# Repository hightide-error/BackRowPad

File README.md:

# BackRowPad, by The Devil's Workshop (a.k.a hightide-error)

![][backrowPad]

[backrowPad]: imgs/backRowPad.png "Photo of a fully-assembled BackRowPad with RGB underglow."

A 12-key linear macropad, designed to replace the back row of function keys or just be a stick of keys you can map to stuff. Open-source and powered by QMK.

There are no maintainers! I designed this macropad and I am not selling it as a product! I am not providing any support! But the design works and you can make your own if you want, so here it is.

**Read through this before getting the boards and assembling!**

## Features

- Keys (wow)
- A cool pattern on the switch plate and backplate
- Optional MX hotswap sockets (no choc support)
- Optional header for an RGB LED strip

## Parts List
The BackRowPad uses pretty standard DIY mechanical keyboard parts.

- **Pro Micro-footprint microcontroller x1:** I'm using Adafruit's KB2040, which is what the firmware is written for. However, any other RP2040 or ATmega32U4 board with a Pro Micro footprint should work: just make appropriate changes to the firmware. You can see pin assignments in the schematic.
- **1N4148 diode x12.**
- **MX mechanical switches x12.**
- **MX keycaps x12** (uniform profile recommended).
- **PTS636 through-hole button switch x1:** this is the standard 'reset switch' used in a variety of DIY mech keyboards. This is optional if your microcontroller has an onboard reset button on top, but it can be nice to have anyway.
- **M2 bolts and standoffs x4 'sets':** The main PCB, switchplate, and baseplate are held together with M2 hardware in each corner. With a 1.6mm thick switchplate, a 3mm standoff between the main PCB and switchplate is nearly perfect: I ended up putting in some 0.4mm 3D-printed spacers just to fully fill the space, but it should be fine without as long as you don't overtighten them. Between the main PCB and baseplate it's really your choice: any standoffs longer than ~7-8mm should work with the reset button in place, but you can probably go shorter if you're omitting it for an onboard-microcontroller button. I'm using 16mm-long M2 standoffs there, both to make the height similar to my main keeb and because I'm routing cables through that space and want it to be reasonably wide.
- **_(Optional)_ Kailh MX hotswap sockets x12:** if you want hotswap, of course.
- **_(Optional)_ RGB LED strip x1:** WS2811, SK6812, etc. (see QMK documentation). I'm using Adafruit's 4mm-wide 'Ultra Skinny NeoPixel 1515' strip, but you should be able to cram in something a bit wider (see pictures). You might also want a right-angled header and corresponding socket for connecting the strip, but that's up to you.

![][rgb]

[rgb]: imgs/backRowPad_RGBstrip.png "Photo of the bottom of the BackRowPad main PCB, with an RGB LED strip connected."

And of course, the board(s). All of these were ordered with 1.6mm thick FR-4 bases, but other thicknesses and types should work.

**It's probably a good idea to order them with a lead-free solder process, especially the switchplate and baseplate since they have a lot of exposed, soldermasked area for the designs**, although I still wouldn't recommend licking them or anything. On JLCPCB, the lead-free HASL option is just a tiny bit more expensive and will increase your lead time by like a day.

The boards also have the "JLCJLCJLCJLC" text on them to specify a location for a JLCPCB order number: if you're using a different fab or are removing the order number, you can just delete that and re-export the fab files.

Finally, your fab may (reasonably) check that the soldermask on the switchplate and baseplate are meant to go off the edge of the board: this is fine, since the pattern is meant to cover the entire area and is cosmetic.

- **BackRowPad main PCB x1** (called backRow_Pad in the KiCAD files).
- **BackRowPad switchplate x1** (called backRow_SwitchPlate in the KiCAD files): technically this is optional if you're soldering 5-pin switches in, but you'll probably want the stability and it has a cool design on it. You can flip it over depending on if you want the black/white design with the board name, or the tiled MX switch design in the soldermask.
- **BackRowPad base plate x1** (called backRow_BasePlate in the KiCAD files): if you have access to a sufficiently-sized lasercutter or 3D printer, you might be better off just taking the hole locations and whipping up a cheaper baseplate instead of one made with a full PCB fab process. But again, it has a cool design on it so yeah.

![][boards]

[boards]: imgs/backRowPad_boards.png "Photo of the three BackRowPad boards. Top to bottom: the switchplate, the main PCB, and the baseplate."

## Assembly

(**Please read through this and look at the images before starting assembly!** It's a pretty simple design, but still).

Assembly is pretty straightforward: the diodes, reset switch, and optional hotswap sockets all have outlines on the silkscreen where they're meant to go (and with what polarity for the diodes). However, for clarity, here's which components go on which side, where the top side is the side with the board info on it ("BackRowPad rev. 0", etc.):

- **TOP:** microcontroller, keyswitches.
- **BOTTOM:** diodes, reset button, optional hotswap sockets, optional RGB header. Also the RGB strip but if you're putting an RGB strip on I'm going to kinda assume you know what you're doing.

![][pcb]

[pcb]: imgs/backRowPad_assembledUnderside.png "Photo of the bottom of the main BackRowPad PCB, assembled with hotswap sockets."

Also, note some things about assembly order:

- **If you're soldering in the switches**, you need to solder the diodes, reset button, and optional RGB header before you solder the switches, since the switchplate will be covering the area you need to solder (I guess it's possible to do, but it'd be a massive pain). As implied, you'll also need to put the switches in the switchplate first, since the switchplate will end up between the lip of the switches and the top of the main PCB. If you're using M-F standoffs to go between the switchplate and PCB, these also need to be in before you solder the switches because you won't be able to manoeuvre them in later. _Also_ note that since the switchplate is being sealed in between, you won't be able to flip it to the other design once everything's soldered, so consider your choice.
  - To be honest I've only assembled this board hotswap so if you're soldering the switches, be careful since you're in uncharted waters!
- Regardless of if you're using hotswap or not, if you're soldering a right-angled RGB header on then you'll want to do that after soldering the microcontroller since it'll block access to that part of the PCB on the bottom.

![][choices]

[choices]: imgs/backRowPad_choices.png "Photo of two BackRowPads fully assembled apart from keycaps. One is taller than the other due to longer standoffs, and they each have the switchplate flipped a different way."

## Bootloader

Use the 'RESET' button mounted on the bottom of the main PCB to reset your microcontroller (or the one onboard your microcontroller, if it has one) and enter the bootloader as per its instructions. For RP2040 devices, this means having BOOTSELECT held down when the board resets.

## License

This design is licensed under [Creative Commons BY-NC-SA 4.0](https://creativecommons.org/licenses/by-nc-sa/4.0/ "CC BY-NC-SA 4.0 Deed").

## That's it!

no questions

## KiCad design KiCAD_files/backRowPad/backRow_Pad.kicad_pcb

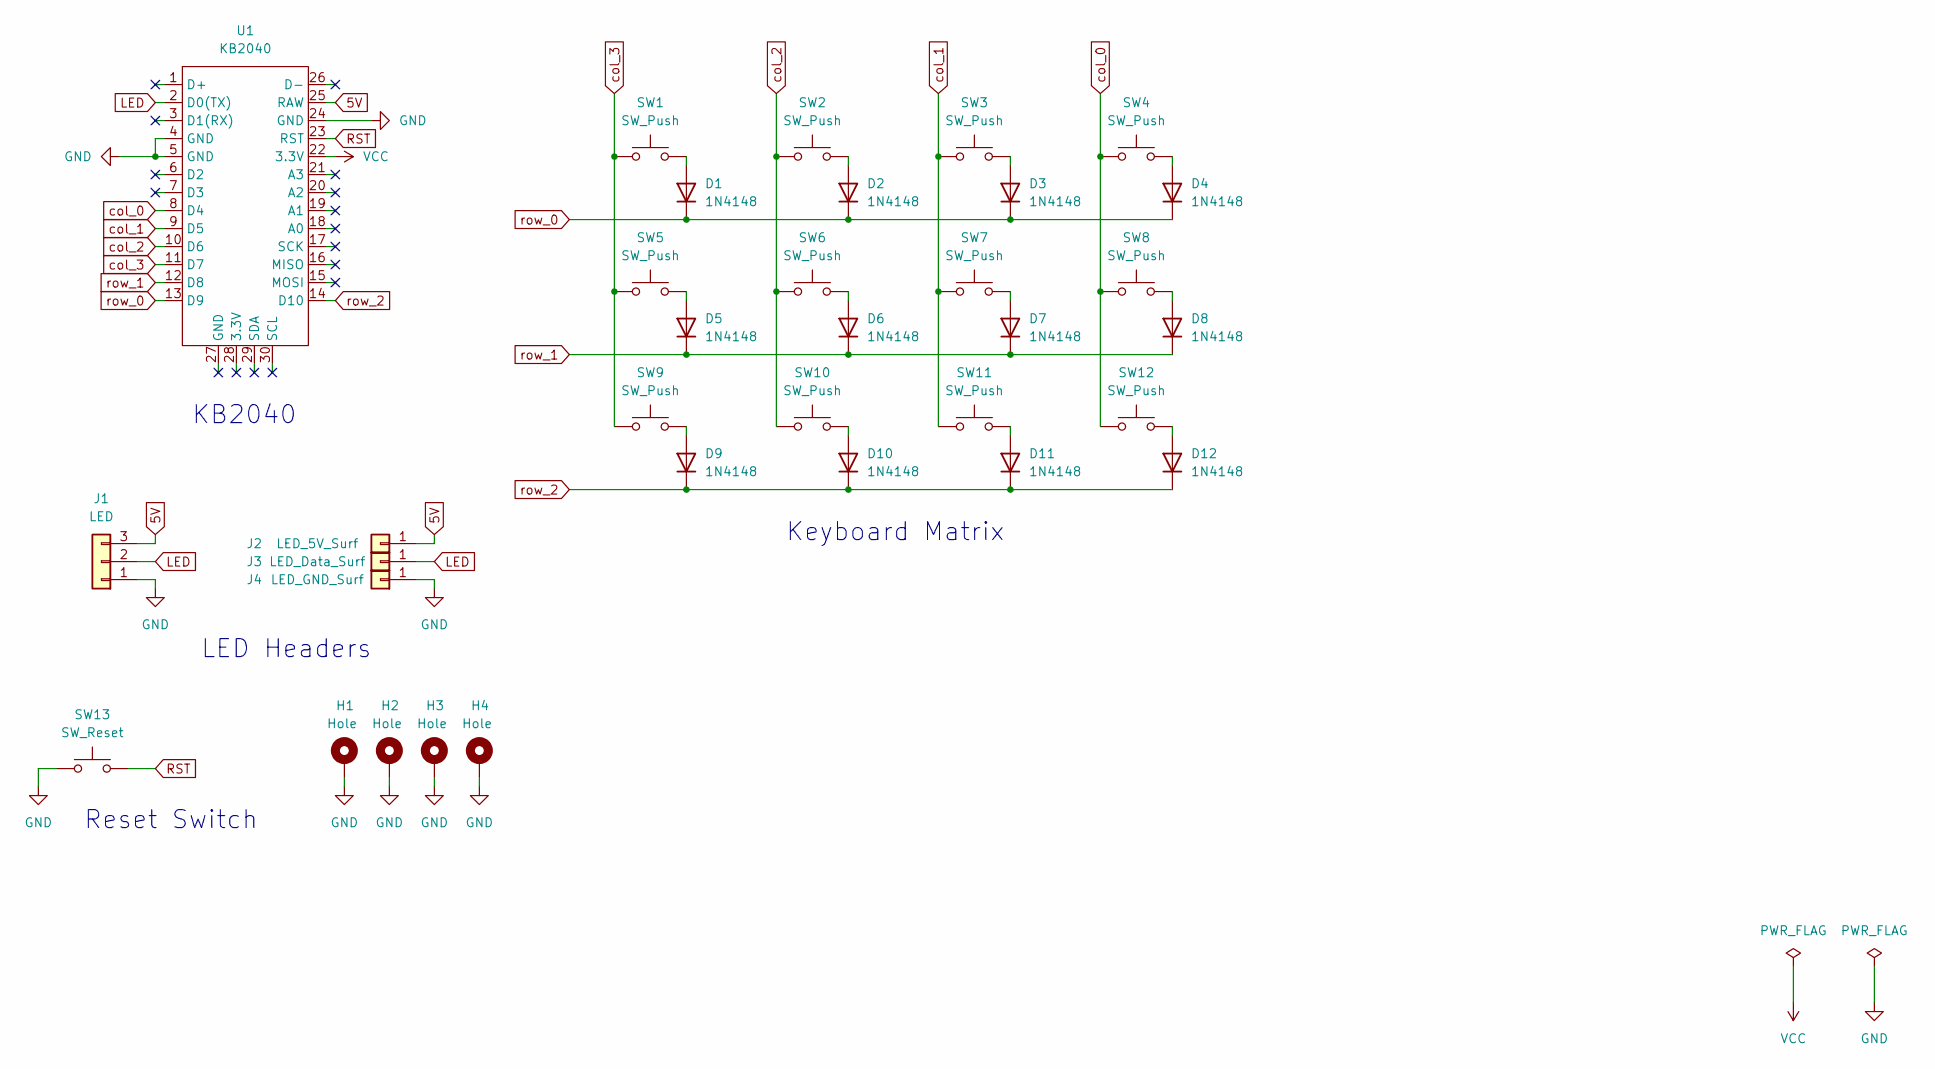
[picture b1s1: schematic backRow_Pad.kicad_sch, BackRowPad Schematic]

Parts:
D1, D2, D3, D4, D5, D6, D7, D8, D9, D10, D11, D12: 1N4148; D_DO-35_SOD27_P7.62mm_Horizontal
H1, H2, H3, H4: Hole; MountingHole_2.2mm_M2_Pad_TopBottom
J1: LED; PinHeader_1x03_P2.54mm_Vertical
J2: LED_5V_Surf; SolderWirePad_1x01_SMD_1x2mm
J3: LED_Data_Surf; SolderWirePad_1x01_SMD_1x2mm
J4: LED_GND_Surf; SolderWirePad_1x01_SMD_1x2mm
SW1, SW2, SW3, SW4, SW5, SW6, SW7, SW8, SW9, SW10, SW11, SW12: SW_Push; Kailh_socket_MX_optional
SW13: SW_Reset; SW_PTS636_THT
U1: KB2040

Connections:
5V: J1.3, J2.1, U1.25 (RAW)
GND: H1.1, H2.1, H3.1, H4.1, J1.1, J4.1, SW13.1, U1.4 (GND), U1.5 (GND), U1.24 (GND)
LED: J1.2, J3.1, U1.2 (D0(TX))
unnamed: D1.2 (A), SW1.2
unnamed: D2.2 (A), SW2.2
unnamed: D3.2 (A), SW3.2
unnamed: D4.2 (A), SW4.2
unnamed: D5.2 (A), SW5.2
unnamed: D6.2 (A), SW6.2
unnamed: D7.2 (A), SW7.2
unnamed: D8.2 (A), SW8.2
unnamed: D9.2 (A), SW9.2
unnamed: D10.2 (A), SW10.2
unnamed: D11.2 (A), SW11.2
unnamed: D12.2 (A), SW12.2
RST: SW13.2, U1.23 (RST)
VCC: U1.22 (3.3V)
col_0: SW4.1, SW8.1, SW12.1, U1.8 (D4)
col_1: SW3.1, SW7.1, SW11.1, U1.9 (D5)
col_2: SW2.1, SW6.1, SW10.1, U1.10 (D6)
col_3: SW1.1, SW5.1, SW9.1, U1.11 (D7)
row_0: D1.1 (K), D2.1 (K), D3.1 (K), D4.1 (K), U1.13 (D9)
row_1: D5.1 (K), D6.1 (K), D7.1 (K), D8.1 (K), U1.12 (D8)
row_2: D9.1 (K), D10.1 (K), D11.1 (K), D12.1 (K), U1.14 (D10)

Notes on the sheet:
Keyboard Matrix
Reset Switch
LED Headers
KB2040

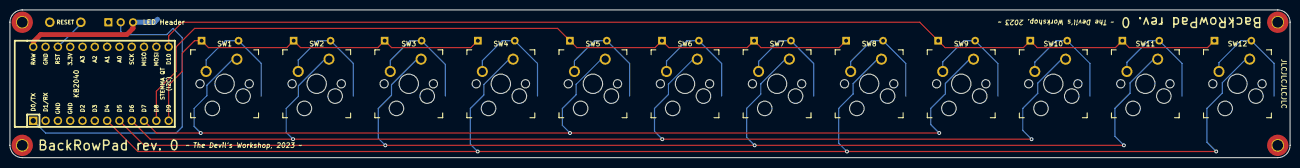
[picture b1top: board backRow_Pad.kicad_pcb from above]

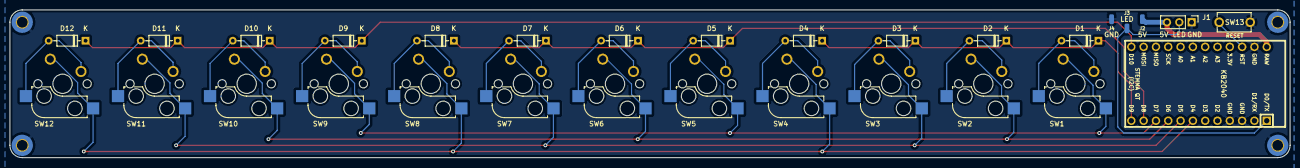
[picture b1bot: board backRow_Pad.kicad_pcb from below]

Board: 2 copper layers, 264.2 x 30.5 mm, 34 parts (17 on the bottom side), 23 nets.

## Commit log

2024-06-04 initial commit to public repo
